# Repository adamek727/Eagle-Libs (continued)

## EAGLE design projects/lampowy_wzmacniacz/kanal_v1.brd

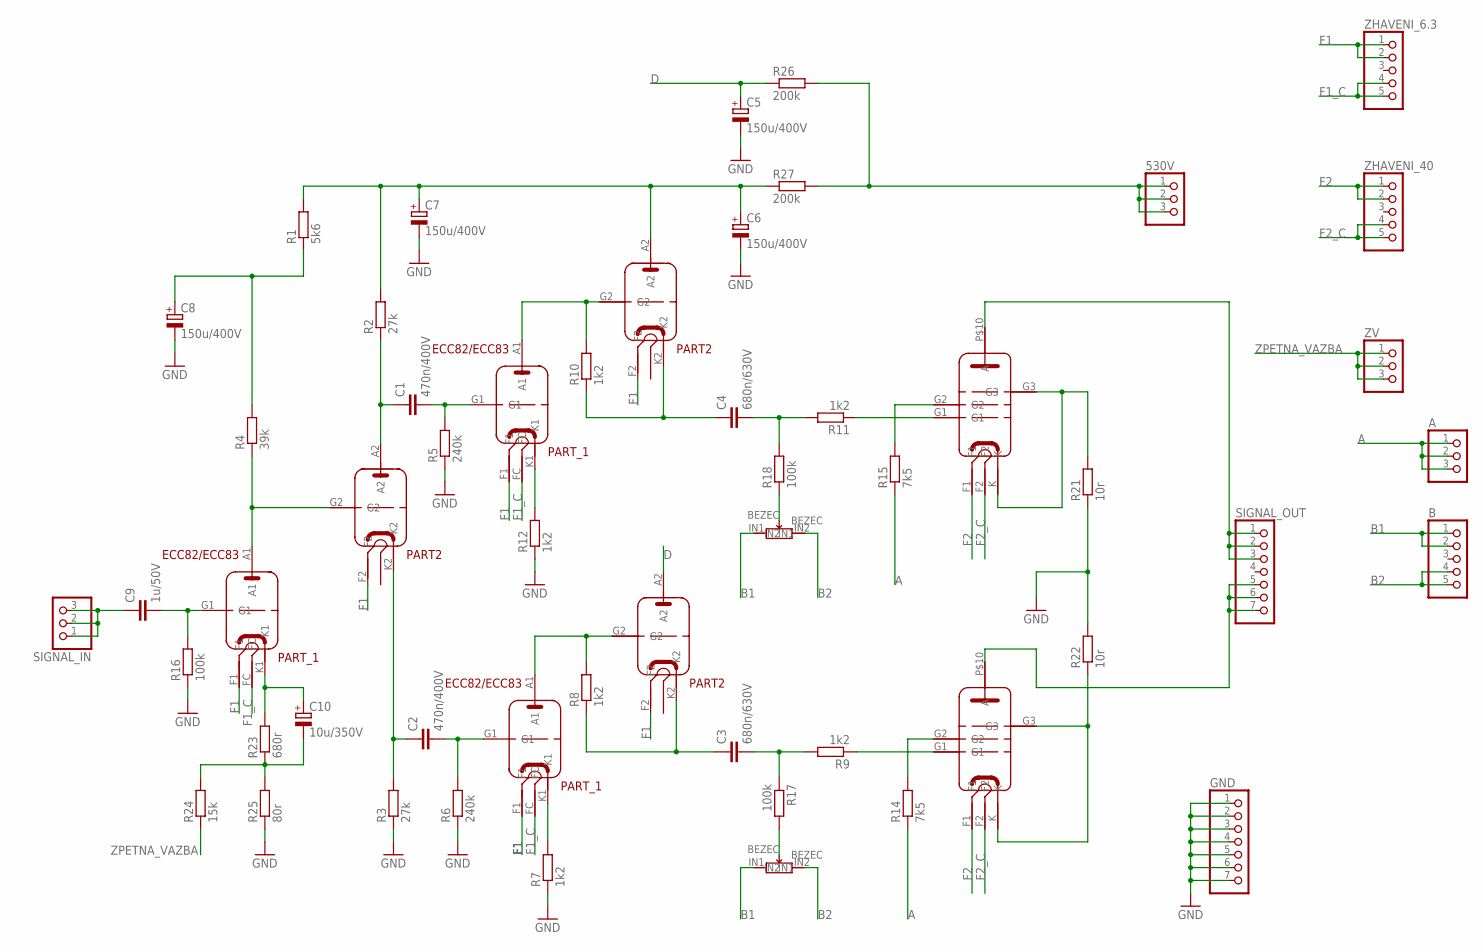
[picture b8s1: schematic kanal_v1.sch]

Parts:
530V: 1X03
A: 1X03
B: 1X05
C1, C2: 470n/400V; C15B7
C3, C4: 680n/630V; C27.5B11
C5, C6, C7, C8: 150u/400V; EB25D
C9: 1u/50V; C5B3.5
C10: 10u/350V; E5-10,5
GND: 1X07
R1: 5k6; 0309/10
R2, R3: 27k; 0309/10
R4: 39k; 0309/10
R5, R6: 240k; 0309/10
R7, R8, R9, R10, R11, R12: 1k2; 0309/10
R14, R15: 7k5; 0309/10
R16, R17, R18: 100k; 0309/10
R21, R22: 10r; 0309/10
R23: 680r; 0309/10
R24: 15k; 0309/10
R25: 80r; 0309/10
R26, R27: 200k; 0309/10
SIGNAL_IN: 1X03
SIGNAL_OUT: 1X07
U$1: ECC82; ECC82_PACKAGE
U$2, U$3: ECC83; ECC82_PACKAGE
U$4, U$5: PL509; PL509_PACKAGE
U$6, U$7: TRIMMER; TRIMMER_15X15_PACKAGE
ZHAVENI_6.3, ZHAVENI_40: 1X05
ZV: 1X03

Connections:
A: A.1, A.2, A.3, R14.1, R15.1
B1: B.1, B.2, U$6.IN1, U$7.IN1
B2: B.4, B.5, U$6.IN2, U$7.IN2
D: C5.+, R26.1, U$3.A2
F1: U$1.F1, U$1.F2, U$2.F1, U$2.F2, U$3.F1, U$3.F2, ZHAVENI_6.3.1, ZHAVENI_6.3.2
F1_C: U$1.FC, U$2.FC, U$3.FC, ZHAVENI_6.3.4, ZHAVENI_6.3.5
F2: U$4.F1, U$5.F1, ZHAVENI_40.1, ZHAVENI_40.2
F2_C: U$4.F2, U$5.F2, ZHAVENI_40.4, ZHAVENI_40.5
GND: C5.-, C6.-, C7.-, C8.-, GND.1, GND.2, GND.3, GND.4, GND.5, GND.6, GND.7, R3.1, R5.1, R6.1, R7.1, R12.1, R16.1, R21.1, R22.2, R25.1
unnamed: C9.2, R16.2, U$1.G1
unnamed: C10.+, R23.2, U$1.K1
unnamed: C10.-, R23.1, R24.2, R25.2
unnamed: R4.1, U$1.A1, U$1.G2
unnamed: C8.+, R1.1, R4.2
unnamed: C1.1, R2.1, U$1.A2
unnamed: C6.+, C7.+, R1.2, R2.2, R27.1, U$2.A2
unnamed: C2.1, R3.2, U$1.K2
unnamed: C1.2, R5.2, U$2.G1
unnamed: C2.2, R6.2, U$3.G1
unnamed: R17.2, U$6.BEZEC
unnamed: R7.2, U$3.K1
unnamed: R8.2, U$3.A1, U$3.G2
unnamed: C3.1, R8.1, U$3.K2
unnamed: C3.2, R9.2, R17.1
unnamed: R9.1, U$5.G1
unnamed: R14.2, U$5.G2
unnamed: C4.1, R10.1, U$2.K2
unnamed: R22.1, U$5.G3, U$5.K
unnamed: R21.2, U$4.G3, U$4.K
unnamed: R10.2, U$2.A1, U$2.G2
unnamed: SIGNAL_OUT.5, SIGNAL_OUT.6, SIGNAL_OUT.7, U$5.P$10 (A)
unnamed: 530V.1, 530V.2, 530V.3, R26.2, R27.2
unnamed: C4.2, R11.2, R18.2
unnamed: R11.1, U$4.G1
unnamed: R18.1, U$7.BEZEC
unnamed: R12.2, U$2.K1
unnamed: C9.1, SIGNAL_IN.1, SIGNAL_IN.2, SIGNAL_IN.3
unnamed: R15.2, U$4.G2
unnamed: SIGNAL_OUT.1, SIGNAL_OUT.2, SIGNAL_OUT.3, U$4.P$10 (A)
ZPETNA_VAZBA: R24.1, ZV.1, ZV.2, ZV.3

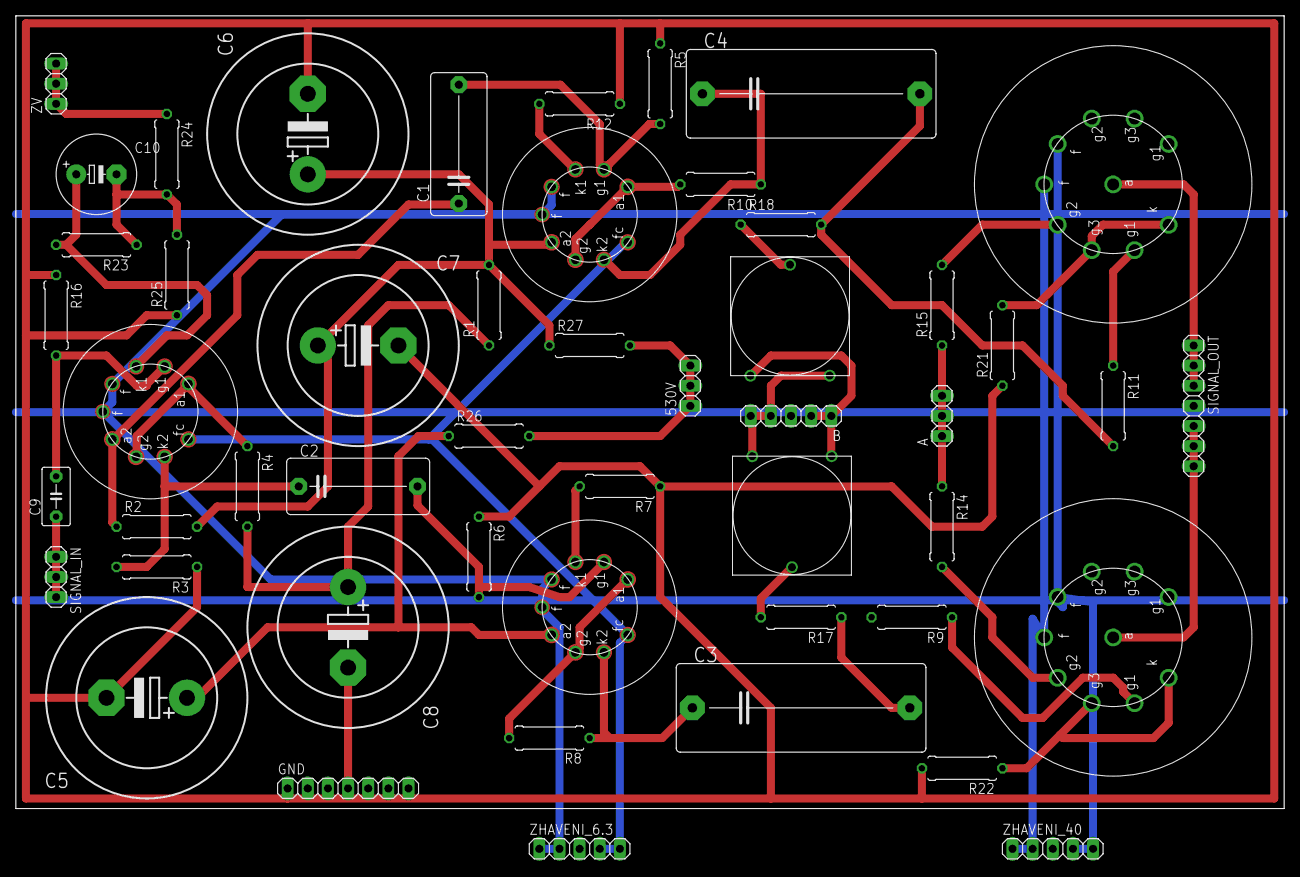
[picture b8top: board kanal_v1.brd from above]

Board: 2 copper layers, 160.0 x 100.0 mm, 50 parts (0 on the bottom side), 40 nets.

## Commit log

2021-03-04 added xt and autofuse libst
2021-03-08 fixed autofuse lib
2021-03-11 added t-dean connector
2021-04-10 added gramofon lib with dcdc converter
2021-04-10 added waldek chassis board
2021-04-10 added my older works
2021-04-12 added power board for new robots
2021-04-12 added jakub charvat board
2021-04-12 updated power_board
2021-04-12 charvat bakalarka minor fixes
2021-04-12 miniaturized chassis board
2021-04-13 moved hole on tank chassis board
2021-06-02 added gnss, imu and barometer modules
2021-06-02 added gnss rpi shield board
2021-06-03 updated walsedk start board and gnss module board
2021-06-17 added bee counter light
2021-06-20 added pzko led project
2021-06-20 bee counter board
2021-07-21 fixed waldek missing pwm outputs, wop on gramofon
2021-07-21 updated gramofon board
2021-07-21 gramofon update
2021-08-26 added cooper to gramophone board
2021-09-08 cleaning
2021-10-26 updated waldek chassis board and added new rpi shield
2021-10-27 minor fixes of waldek 2 chassis board and rpi shield
2021-11-16 added tube amplifier
2022-05-16 added keystone 1018 battery
2022-05-17 updated battery library and added battery backup board
2022-05-17 upgraded gramofon board
2022-05-17 reduced gramofon board size
2022-07-01 updated asgard power board
2022-07-01 updated battery board
2023-07-16 added palirna
2023-07-21 added universal board
